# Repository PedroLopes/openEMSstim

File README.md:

#### Navigating the openEMSstim repository:

* [This page = official](https://github.com/PedroLopes/openEMSstim/): your starting point to the official & maintained code.
* [UIST 2016](https://github.com/PedroLopes/openEMSstim/tree/UIST2016): a sub branch containing the student projects from ACM UIST 2016 SIC. 
* [simple-multiplexer](https://github.com/PedroLopes/openEMSstim/tree/simple-multiplexer): a sub branch that offers a simple multiplexer from 2 to 5 channels using relays.

# openEMSstim: open-hardware module to adjust the intensity of EMS/TENS stimulators. 

This is the openEMSstim, a **hardware board** based on an Arduino Nano that modulates the amplitude of Electrical Muscle Stimulation (EMS) signals. Here you also find the **software** that communicates with the board and controls it (android, unity, etc). This board is controllable via *Bluetooth* and compatible with any *BLE* device you have (such as your smartphone). It also is controllable via *Serial* (USB) by plugging in a USB cable from your computer to the *Arduino Nano* on the board. 

## Getting started (tutorial)

All the necessary information for getting started is compiled in a step-by-step tutorial, [start here](start-here-tutorials/1.getting_started_step_by_step.md). 

## Why this hardware?

The openEMSstim is a derivative by [Pedro Lopes](http://plopes.org) of the awesome [EMS toolkit](https://bitbucket.org/MaxPfeiffer/letyourbodymove/wiki/Home). See the License which acknowledges all the work from the original makers. This project is forked to (1) provide a simpler design with a few changes, (2) preserve the original design and credit without pulling all the changes to it and (3) be used in the [UIST Student Innovation Contest 2016](https://uist.acm.org/uist2016/contest) without needing to change the instructions of the original project which is meant for HCI researchers and not for a UIST student audience. If you want to see the projects created by the students at UIST 2016 using this repo, see [here](http://plopes.org/ems/) (see the source code [here](https://github.com/PedroLopes/openEMSstim/tree/UIST2016/UIST2016-projects)).
 	
## Read before using
* Read the [LICENSE](https://bitbucket.org/MaxPfeiffer/letyourbodymove/wiki/Home/License)
* Make sure you follow the safety instructions before using it and you are familiar with all the procedure of how to apply EMS safely.
* If you are not familiar with EMS: [start here (slides,papers,examples)](https://www.dropbox.com/s/rg6vpg9fhgn91fe/CHI_Course_Slides_2016PedroLopes_MaxPffeifer.pptx)
* Please note that this board does not generate any EMS signal, it is a amplifier that can only reduce the power of the signal you input to it. You need a EMS signal generator too, this will be your input. For your safety, use only: an off-the-shelve, un-modded, original, regulation-approved, medically compliant device. 
* Please pair this board only with medically compliant EMS devices (check regulation in your country) and verify that you plug it in the INPUT port marked in the board. The OUTPUT port is connected to the electrode pads. 
* Please use EMS electrodes (wet, pre-gelled and approved electrodes). 

## Supported platforms & APIs

openEMSstim can be interfaced on virtually anything as long as the device features bluetooth (BT LE) or serial (USB). Here are the languages and libraries for which we have created examples and tested the code:

### Authors of this repo's software, casings & hardware
* Pedro Lopes <plopesresearch@gmail.com> (software, cases, hardware remix, videos)
* Doğa Yüksel <dogayuksel@gmail.com> (cases)
* Sijing You <sijing.you@student.hpi.uni-potsdam.de> (testing)

### External Contributors
* Steffen Norbert Franz Blümm <steffen-norbert-franz.bluemm@stud.uni-bamberg.de> (iOS code)
* Fushimi Ryohei <fushimi.ryohei@gmail.com> (node.js fixes)

### Authors from the original board design (EMS Toolkit)
* copyright 2016 by Tim Dünte <tim.duente@hci.uni-hannover.de>
* copyright 2016 by Max Pfeiffer <max.pfeiffer@hci.uni-hannover.de>

### Original License 
Licensed under "The MIT License (MIT) – military use of this product is forbidden – V 0.2" by the makers Max Pfeiffer & Tim Dünte, all original designs fully credited to the makers. 
Some rights reserved. See [LICENSE](https://bitbucket.org/MaxPfeiffer/letyourbodymove/wiki/Home/License>)

### Sponsors

The openEMSstim software and the hardware for the ACM UIST Student Innovation Contest 2016 was kindly sponsored by the [Hasso Plattner Institute](http://hpi.de/en.html).

### Liability

Please refer to the liability waiver (in documentation/liability_waiver.md).

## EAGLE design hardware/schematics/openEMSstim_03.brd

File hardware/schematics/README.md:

# openEMSstim: the schematics 

The openEMSstim is a mod by [Pedro Lopes](plopes.org) of the [EMS toolkit](https://bitbucket.org/MaxPfeiffer/letyourbodymove/wiki/Home). See the License which acknoledges all the work from the original makers. This project is forked to (1) provide a simpler design with a few changes, (2) preserve the original design and credit without pulling all the changes to it and (3) be used in the [UIST Student Innovation Contest 2016](https://uist.acm.org/uist2016/contest) without needing to change the instructions of the original project which is meant for HCI researchers and not for a UIST student audience. 	
## How to open the schematics
These were done in **Eagle**. So that will be the easiest. Eagle is free to use but not open source, for that matter we are trying to migrate these schematics to a KiCad format which fits better with the nature of this project. Hang in there or help us by doing it and sending us a pull request. 

## Status
Note that V3 hasn't been tested. If you want a stable version, roll back to V2 by doing:
``git checkout 3d5f0cdcc33ded0a633e556be4b3511867ce1fb2``

## Detailed differences to the original board (openEMSstim_03)
1. Diode protection against reverse polarity (using http://www.mouser.com/ds/2/302/1PS70SB10-838739.pdf)
2. Marked + and - on the board layout, so you know how to plug the battery
3. ON/OFF slider switch (using http://www.alps.com/prod/info/E/HTML/Switch/Slide/SSSS8/SSSS810701.html)
4. (more to come, see hardware specifications in the tutorials folder) 

### License and Liability

Please refer to the liability waiver (in documentation/liability_waiver.md).

Please refer to the license (in /license.md)

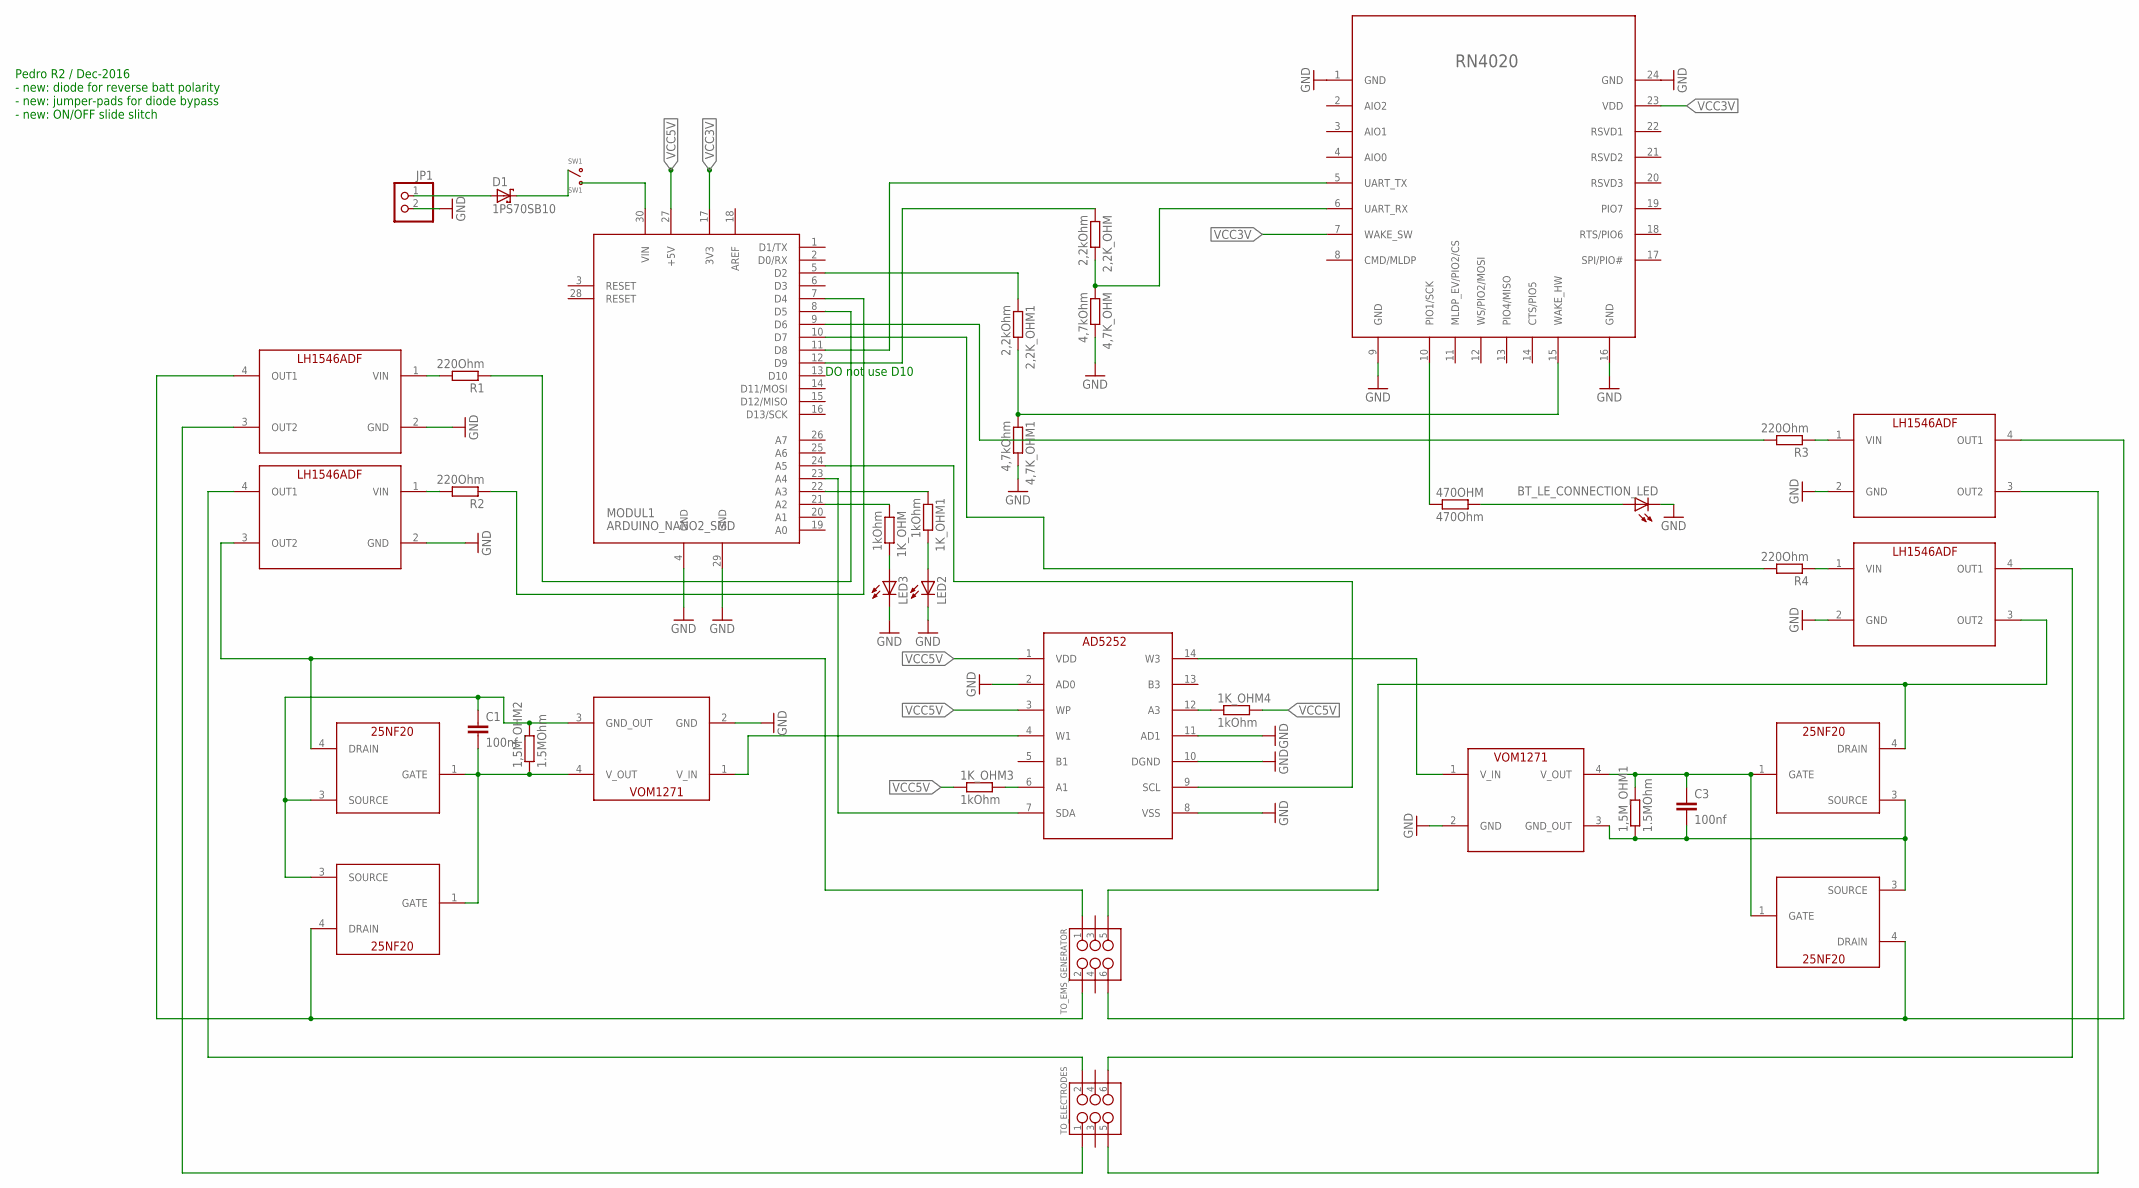
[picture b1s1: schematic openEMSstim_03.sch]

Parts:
1,5M_OHM1, 1,5M_OHM2: 1.5MOhm; R0805
1K_OHM, 1K_OHM1, 1K_OHM3, 1K_OHM4: 1kOhm; R0805
2,2K_OHM, 2,2K_OHM1: 2,2kOhm; R0805
4,7K_OHM, 4,7K_OHM1: 4,7kOhm; R0805
470OHM: 470Ohm; R0805
BT_LE_CONNECTION_LED: LEDCHIPLED_0603; CHIPLED_0603
C1, C3: 100nf; 0805
D1: 1PS70SB10; SOT323
JP1: PINHD-1X2; 1X02
LED2, LED3: LEDCHIPLED_0603; CHIPLED_0603
MODUL1: ARDUINO_NANO2_SMD
MOS01, MOS02, MOS03, MOS04: DEV; PACK
R1, R2, R3, R4: 220Ohm; R0805
SW1: SW1; SSSS810701
TO_ELECTRODES: M03X2; RIGHT_ANGLED_SHROUED_2X06_6PIN
TO_EMS_GENERATOR: M03X2; RIGHT_ANGLED_SHROUED_2X06_6PIN
U$5: RN4020
U$6: AD5252; TSSOP
U$9, U$10: VOM1271; SOP04
U$11, U$12, U$13, U$14: LH1546ADF; DIP04-SMD

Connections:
AREF: MODUL1.18 (AREF)
GND: 4,7K_OHM.2, 4,7K_OHM1.2, BT_LE_CONNECTION_LED.C, JP1.2, LED2.C, LED3.C, MODUL1.4 (GND), MODUL1.29 (GND), U$5.1 (GND), U$5.9 (GND), U$5.16 (GND), U$5.24 (GND), U$6.2 (AD0), U$6.8 (VSS), U$6.10 (DGND), U$6.11 (AD1), U$9.2 (GND), U$10.2 (GND), U$11.2 (GND), U$12.2 (GND), U$13.2 (GND), U$14.2 (GND)
unnamed: U$6.4 (W1), U$9.1 (V_IN)
unnamed: 1K_OHM.1, MODUL1.21 (A2)
unnamed: MODUL1.23 (A4), U$6.7 (SDA)
unnamed: TO_ELECTRODES.6, U$14.4 (OUT1)
unnamed: 2,2K_OHM.2, 4,7K_OHM.1, U$5.6 (UART_RX)
unnamed: 2,2K_OHM.1, MODUL1.12 (D9)
unnamed: TO_ELECTRODES.1, U$11.3 (OUT2)
unnamed: 1,5M_OHM2.1, C1.2, MOS01.1 (GATE), MOS02.1 (GATE), U$9.4 (V_OUT)
unnamed: MODUL1.11 (D8), U$5.5 (UART_TX)
unnamed: MODUL1.24 (A5), U$6.9 (SCL)
unnamed: MODUL1.30 (VIN), SW1.1 (B)
unnamed: R2.2, U$12.1 (VIN)
unnamed: TO_ELECTRODES.2, U$12.4 (OUT1)
unnamed: R1.2, U$11.1 (VIN)
unnamed: R3.1, U$13.1 (VIN)
unnamed: R4.1, U$14.1 (VIN)
unnamed: MODUL1.8 (D5), R1.1
unnamed: MODUL1.7 (D4), R2.1
unnamed: MODUL1.9 (D6), R3.2
unnamed: MODUL1.10 (D7), R4.2
unnamed: MOS01.4 (DRAIN), TO_EMS_GENERATOR.1, U$12.3 (OUT2)
unnamed: U$6.14 (W3), U$10.1 (V_IN)
unnamed: 1,5M_OHM1.2, C3.1, MOS03.1 (GATE), MOS04.1 (GATE), U$10.4 (V_OUT)
unnamed: 1,5M_OHM1.1, C3.2, MOS03.3 (SOURCE), MOS04.3 (SOURCE), U$10.3 (GND_OUT)
unnamed: 1K_OHM4.1, U$6.12 (A3)
unnamed: 1,5M_OHM2.2, C1.1, MOS01.3 (SOURCE), MOS02.3 (SOURCE), U$9.3 (GND_OUT)
unnamed: MOS03.4 (DRAIN), TO_EMS_GENERATOR.5, U$14.3 (OUT2)
unnamed: MOS02.4 (DRAIN), TO_EMS_GENERATOR.2, U$11.4 (OUT1)
unnamed: TO_ELECTRODES.5, U$13.3 (OUT2)
unnamed: MOS04.4 (DRAIN), TO_EMS_GENERATOR.6, U$13.4 (OUT1)
unnamed: 2,2K_OHM1.2, 4,7K_OHM1.1, U$5.15 (WAKE_HW)
unnamed: 1K_OHM3.2, U$6.6 (A1)
unnamed: 2,2K_OHM1.1, MODUL1.5 (D2)
unnamed: 470OHM.1, U$5.10 (PIO1/SCK)
unnamed: 470OHM.2, BT_LE_CONNECTION_LED.A
unnamed: 1K_OHM1.2, LED2.A
unnamed: 1K_OHM1.1, MODUL1.22 (A3)
unnamed: 1K_OHM.2, LED3.A
unnamed: D1.1 (A), JP1.1
unnamed: D1.3 (K), SW1.2 (COM)
VCC3V: MODUL1.17 (3V3), U$5.7 (WAKE_SW), U$5.23 (VDD)
VCC5V: 1K_OHM3.1, 1K_OHM4.2, MODUL1.27 (+5V), U$6.1 (VDD), U$6.3 (WP)

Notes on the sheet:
DO not use D10
Pedro R2 / Dec-2016 - new: diode for reverse batt polarity - new: jumper-pads for diode bypass - new: ON/OFF slide slitch

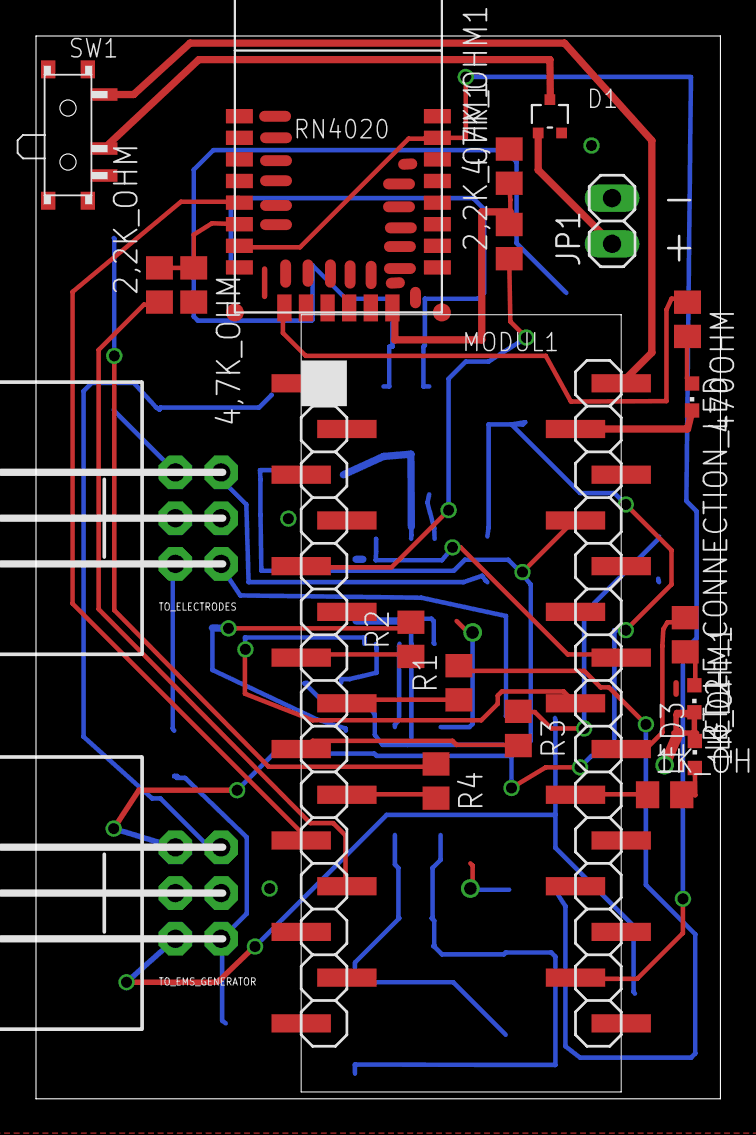
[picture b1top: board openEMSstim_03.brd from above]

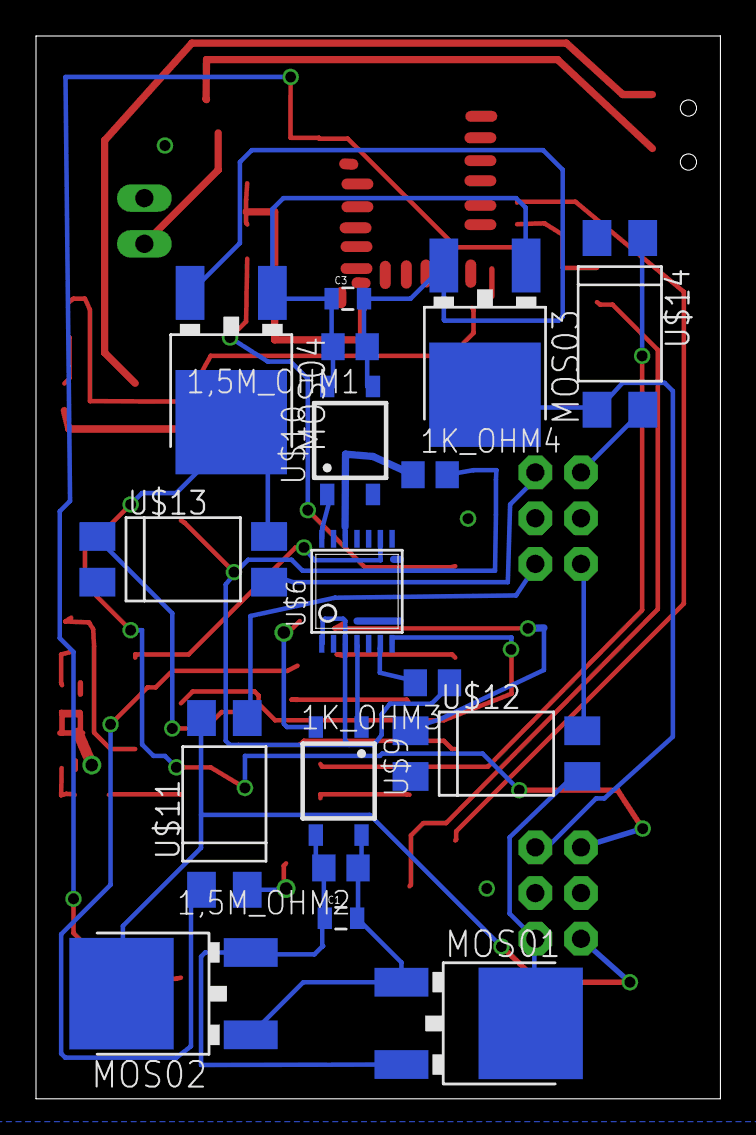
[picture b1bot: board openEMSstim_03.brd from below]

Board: 2 copper layers, 38.0 x 59.0 mm, 38 parts (17 on the bottom side), 43 nets.

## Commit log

2015-05-07 new file
2016-06-10 working on hardware guide
2016-06-10 protocol details enhanced
2016-06-10 README improved
2016-06-10 observations about TENS machiens
2016-06-10 renaming
2016-06-12 working on guides
2016-06-12 potential questions that might arise
2016-06-13 working on a very detailed tutorial
2016-06-13 added a file to detail how to better and safely explore the EMS parameters
2016-06-13 worked out on tutorial getting denser and denser, might need a somplification pass later
2016-06-13 renaming main files
2016-06-14 added a qr code, pass on tutorial, added liability placeholders, added new directory, started working on eagle v2
2016-06-14 shifted things and renamed to openEMSstim
2016-06-14 renamed
2016-06-14 changed names again
2016-06-14 logo V1
2016-06-14 logo credits
2016-06-14 started by adding a README
2016-06-14 deleded confusing items
2016-06-14 added license from the original makers, with this I intend to give them credit for all the original designs and preserve their license
2016-06-14 added cases for the openEMSstim
2016-06-14 a gitignore for the project
2016-06-14 started all tutorials
2016-06-14 added a logo
2016-06-14 added info and logo to readme
2016-06-14 improved walkthrough
2016-06-14 reshuffled dirs and names
2016-06-15 minor
2016-06-15 liability waiver
2016-06-15 new qr code
2016-06-15 minor link was wrong
2016-06-16 //#include Arduino_Software.h is it still needed? investigating that as we speak
2016-06-16 //#include Arduino_Software.h was not needed and hanced removed for code simplicity
2016-06-28 logo
2016-06-29 improved readme
2016-06-29 ignore for eagle added
2016-06-29 added the schematic and board file, based on the original open source version but with some changes
2016-06-29 first how to images, will do better later
2016-06-29 some ideas for the new version of the protocol
2016-06-30 changed dir names
2016-06-30 improving how to
2016-06-30 images added, great
2016-06-30 images for tutorial
2016-07-01 logo changed why?
2016-07-01 changed the board, minor change, just a label to orient the arduino while positioning it
2016-07-04 working on detailed ems tutorial
2016-07-04 waveform details and example
2016-07-05 what not to do guide
2016-07-05 new logo 200px scaled
2016-07-05 minor tweaks and missing URLs
2016-07-05 ems params
2016-07-05 a word on schematics
2016-07-06 there is a sync problem with 4.
2016-07-06 logo for android version
2016-07-07 forked the control app from orginal makers and simplified a lot
2016-07-07 readme for android
2016-07-07 minor code update with license to the respective authors
2016-07-07 works p5
2016-07-08 changing On_off basics to have two buttons and only one channel
2016-07-08 added a copy of the On_off that works, maybe I can get the two EMS devices, hence four channel, mode working
2016-07-09 OnOff works
2016-07-09 processing dependencies
2016-07-09 minor for processing install
2016-07-09 minor for android bon install
2016-07-09 openEMSstim was on testerMode and not runnable/working, fixed
2016-07-09 also apk
2016-07-11 added a full command mode to the USB comunication, needs testing
2016-07-11 changed the arduino to be able to parse direct commands that are not in HEX format, still HEX format is available via USB or BT, on USB it now accepts string commands directly as dictated by protocol
2016-07-11 started bulding up python support via USB
2016-07-11 python command creator works and is tested
2016-07-11 added an ems pong game, needs an ems lib for python to abstract stuff
2016-07-11 python readme
2016-07-11 started the python module
2016-07-12 working on pyEMS module and test case
2016-07-12 missing raise exception and value for init
2016-07-12 solved issue with __init__ but not tested yet
2016-07-12 updated tutorial to use the lib, much better
2016-07-12 pong with EMS works
2016-07-12 images
2016-07-12 readme for pong
2016-07-12 pong comments
2016-07-12 lib for python
2016-07-12 added a list of ideas to dev branch
2016-07-12 reorganized image folder
2016-07-12 cleaned schematics folder
2016-07-12 created some nodejs examples
2016-07-12 fixed examples
2016-07-12 example with server that controls the EMS impulses
2016-07-12 skeleton for nodejs server, had no internet, did without test
2016-07-12 changed to sendfile imstead of sendFile because was throwing an error, i know its deprecated but using old instead
2016-07-12 almost, duration not being sent but othrwise works fine
2016-07-12 added modules
2016-07-13 platform logos
2016-07-13 typos
2016-07-13 nodejs version now works with all fields, fixed bug on duration
2016-07-13 typos fixed on readmes
2016-07-13 fixed bug on channel 0 on nodejs, must be channels 1 and 2
2016-07-13 new nodejs explanation on README
2016-07-13 cases polish images
2016-07-13 typos on readmes
2016-07-13 passed next protocol to collecting ideas list on dev branch
2016-07-13 typos fixed
2016-07-13 documentation added
2016-07-13 typo
2016-07-13 more details on documentation
2016-07-14 refactored test commands
2016-07-14 started playing around with waits on bluetooth side, 200 ms is maybe too long, specially those multipliers
2016-07-14 refactored command debug on EMSSysem.cpp
2016-07-14 idea for faster boot
2016-07-14 cleaned up dev branch
2016-07-14 added intensity information, changed colors, and saved last blutooth device ID
2016-07-14 button colors match the on-board LED colors
2016-07-15 new images from new video tutorial
2016-07-15 changed img
2016-07-15 better walkthrough
2016-07-15 illustrations will now live on dev branch
2016-07-22 new video
2016-07-26 detail about intensity
2016-07-26 added reqs
2016-07-26 requirements.txt added
2016-07-26 added serial port config
2016-07-26 fixed import
2016-07-26 fixed channel number on input string
2016-07-26 typo on 41
2016-07-26 Added a new Pong Game for Processing, via USB
2016-07-26 added pong game for processing and USB
2016-07-26 added wait of 10s for processing and USB
2016-07-26 unity example via USB
2016-07-26 images for walkthrough for unity3d
2016-07-26 tutorial for unity3d
2016-07-27 new apk was crashing on samsung 4.2.4
2016-07-27 USB tutorials pointers
2016-07-28 thanks CJ for testing
2016-07-31 links to new videos
2016-08-01 new idea for android notifications
2016-08-08 started porting a basic calibrate tool for python
2016-08-10 working on basic calub routine
2016-08-12 new calibration routine with commands
2016-08-16 calibration for python now repeats last command
2016-08-16 printing history is incorrect
2016-08-16 printing history is now working
2016-08-19 calibration still undergoing
2016-08-21 working con calibrate
2016-08-21 added some ideas about cables for next go
2016-08-22 calibrate now has shortcuts to increase decrease commands
2016-08-22 working on bill of materials as requested by a student team
2016-08-24 calibration cleaner now
2016-08-24 added a Bill of Materials
2016-08-24 bill of materials updated
2016-09-06 hardware add ons
2016-09-15 calibrate is not complete but these classes were missing
2016-09-16 connectors
2016-09-16 preset had a bug
2016-09-16 added the calib.ems file
2016-09-29 new android permissions might need manual activation
2016-10-06 commit in behalf of Steffen Norbert Franz Blümm who was so kind to do a ios app for openEMSstim
2016-10-07 typical node project don't include node_modules - instead type `npm install`
2016-10-07 existing node_modules dir conflicts with up-to-date node/npm (6.7.0)
2016-10-07 remove node_modules
2016-10-07 move .gitignore to parent directory
2016-10-07 now works with up-to-date node-serialport library
2016-10-07 add packages on package.json
2016-10-07 add package.json
2016-10-07 unused var after pull request @sidestepism that was throwing an error, removed:
2016-10-07 added new contributors
2016-10-07 added contributors
2016-10-09 UIST 2016 branch to host student projects
2016-12-13 connection diagram
2016-12-16 new board design V3: not tested yet
2016-12-16 v3 components
2016-12-16 added eagle ignores
2016-12-16 added some examples and source code from UIST 2016 students
2017-01-13 more things to do
2017-01-24 fixed bug on tester sinhgle-char commands
2017-01-25 deploy code started
2017-01-25 testing still the deploy firmware
2017-01-26 working outside on insane file manip
2017-01-26 working on deploy script
2017-01-26 git clean from ino deploys
2017-01-26 most of the ino workflow works now
2017-01-27 adding test logger
2017-01-27 works kinda nice now, details missing
2017-01-27 working on logging
2017-01-30 ignore logs
2017-02-01 trying to ignore a few unity things
2017-02-01 besides fabbing, i fixed unity3d pong example
2017-02-01 more info on switch and diode
2017-02-01 this is not the last version
2017-02-01 image for switch
2017-02-02 changed a few things to accept three types of serial messages: BT, USB w/ full command or USB w/ single char test mesages
2017-02-02 polished adding new components
2017-02-04 changed default id
2017-02-04 finding bugs
2017-02-06 Added functionality to multiplex output channels
2017-02-06 Enabled full command and test commands
2017-02-17 new ideas
2017-02-21 simple multiplexer using relays made by @cybershubham
2017-02-21 added info about branches

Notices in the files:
parts and their libraries:
SparkFun-Passives: Licensing: Creative Commons ShareAlike 4.0 International - https://creativecommons.org/licenses/by-sa/4.0
